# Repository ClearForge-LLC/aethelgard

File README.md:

# Aethelgard

Generates a circuit board and the firmware that drives it from one specification, and refuses to call either finished until the pair has survived simulated electrical and software faults together, before any board is manufactured.

**Status:** phases P0 to P2 are complete. P3's work has merged, and its exit gate waits on the bench rows that need the sensors (first silicon ran on 2026-11-16). P4's flight-controller work is under way. P5, a second chip family and firmware ecosystem judged as one combination (`docs/northstar.md` §3.1), waits on its trigger. **Use the engine image by its digest, as the Quickstart below does: it is the supported interface.** The crates.io release is 0.3.0 (2026-11-28), all eleven crates: `cargo install aethelgard-cli --version 0.3.0 --locked` installs `aethelgard`, which reads specification 31. Like every release it is a pinned snapshot with no update promise (`RUL-21`), and `main` moves past it. From one specification, `aethelgard` does five things:

- solves the pin assignment;
- emits a schematic and a placed, routed board that pass KiCad's ERC and DRC;
- generates a typestate board crate whose register effects Kani proves (`aethelgard generate` writes it; `aethelgard verify` proves the generated harness);
- boots generated firmware in Renode;
- serves all of this over MCP.

P2 added analog co-simulation, fault campaigns, an archive that replays, and `attribute`, which names the electrical or software half a failure belongs to. **Its rise times are computed by ngspice from the specification's declared pull-up and capacitance bound, not measured on the routed board** (`docs/architecture.md` `RUL-19`); P3 added `extract`, an upper bound on each I2C line's capacitance read from the routed board and judged against that declared bound, as a gate of `aethelgard verify`; `verify --fab-out` writes the reference probe's fabrication package only when every gate passes, and its verdict names every file's hash. No board has been made from it; the bench comparison waits for the development board. The code is licensed `MIT OR Apache-2.0` (see `LICENSE-MIT` and `LICENSE-APACHE`). KiCad's vendored symbols and footprints, in `crates/aethelgard-kicad-lib`, stay `CC-BY-SA-4.0`. Boards emitted from them carry no obligation.

## Where to go

| I want to know | Read |
|---|---|
| Why this exists and what must stay true | [`docs/northstar.md`](docs/northstar.md) |
| What it is and how it is shaped | [`docs/architecture.md`](docs/architecture.md) |
| What order it gets built in, and what "done" means | [`docs/roadmap.md`](docs/roadmap.md) |
| The planning conversation these were synthesized from | [`docs/inputs/argon-session/`](docs/inputs/argon-session/) |

## Quickstart

With only Docker, `bash`, `curl` and `sha256sum`: this block fetches the pinned reference specification, pulls the engine image by digest, and shows the reference board pass ERC and DRC and a doubly-assigned pin refused by name. CI runs exactly this block (`.github/workflows/quickstart.yml`), so it cannot drift. The block is one subshell with `set -euo pipefail`, so pasted into a terminal it stops at the first failed check and never closes your shell.

<!-- quickstart:begin -->
```bash
(
set -euo pipefail
IMAGE=ghcr.io/clearforge-llc/aethelgard@sha256:59e9f0aa2e1ee6ab48aa12855b659fae7ca9a5e9a43046f9d1c1cede9ffdce62
SPEC=https://raw.githubusercontent.com/ClearForge-LLC/aethelgard/10806528ce75ab9b17fdf09f5eda360ae78c7cf8/examples/sentinel-01-minimal.json

# The reference specification, checked against its hash.
curl -fsSL -o spec.json "$SPEC"
echo "03a82a043d459930e254adf5ef24bc5899efe2f5507d29e1c717f315c7bfe7ea  spec.json" | sha256sum -c -

docker pull -q "$IMAGE"
# HOME is the run directory, so the CLI's scratch is private to you (AET-WO-1601).
ae() { docker run --rm --user "$(id -u):$(id -g)" -e HOME=/work -v "$PWD:/work" -w /work "$IMAGE" aethelgard "$@"; }

# Emit the schematic, bill of materials and routed board (exit 0).
emit=$(ae emit --file spec.json --out out); echo "$emit"
grep -q '"ok":true' <<< "$emit"

# ERC on the schematic: exit 0 and a pass verdict.
erc=$(ae check erc --schematic out/sentinel-01.kicad_sch); echo "$erc"
grep -q '"verdict":"pass"' <<< "$erc"

# DRC on the board, judged by the rules the specification declares (board.rules), with schematic parity.
drc=$(ae check drc --board out/sentinel-01.kicad_pcb --spec spec.json --schematic out/sentinel-01.kicad_sch); echo "$drc"
grep -q '"verdict":"pass"' <<< "$drc"
grep -q '"findings":\[\]' <<< "$drc"

# Claim one pin twice (the I2C data line and the flash chip select, both on PB9). solve refuses: exit 2.
docker run --rm --user "$(id -u):$(id -g)" -v "$PWD:/work" -w /work "$IMAGE" python3 -I -c '
import json
s = json.load(open("spec.json"))
s["i2c_buses"][0]["sda"]["pin"] = "PB9"
s["spi_devices"][0]["cs"]["pin"] = "PB9"
json.dump(s, open("double.json", "w"))'
rc=0; refused=$(ae solve --file double.json) || rc=$?; echo "$refused"
[ "$rc" -eq 2 ]
grep -q '"kind":"PinClaimedTwice"' <<< "$refused"
grep -q '"claimants":\["i2c_buses\[0\].sda","spi_devices\[0\].cs"\]' <<< "$refused"
echo "quickstart ok"
)
```
<!-- quickstart:end -->

## Running it

**From crates.io, with no image:** `cargo install aethelgard-cli --version 0.3.0 --locked`. `validate` and `solve` are pure Rust and need no external tool; the release reads specification 31:

```bash
aethelgard validate < examples/sentinel-01-minimal.json   # {"ok":true,...}, exit 0
```

Everything that runs KiCad, Renode, ngspice or Kani (`check erc`, `check drc`, the twin, `prove`, `verify`) needs those tools, which the image above carries, and runs them only inside the CLI's own sandbox; without them the CLI refuses with a named kind and a nonzero exit (the codes are in [`crates/aethelgard-cli/README.md`](crates/aethelgard-cli/README.md)). For a checked board, use the image.

From a clone:

Check a specification. It prints one line of JSON and exits 0 when the specification is valid, nonzero otherwise; the codes are in [`crates/aethelgard-cli/README.md`](crates/aethelgard-cli/README.md).

```bash
cargo run -q -p aethelgard-cli -- validate < examples/sentinel-01-minimal.json
```

---

This README points; it does not define. The invariants, the rulings, and the phases each have exactly one home above, and a copy here would be a fourth place for the same fact to drift.

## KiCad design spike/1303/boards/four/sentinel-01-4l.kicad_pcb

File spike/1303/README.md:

# AET-WO-1303 spike probes (deleted at the build)

Python 3 with numpy, scipy (any recent); no network. Run from each directory.

- `boards/`: `aethelgard emit` of `examples/sentinel-01-minimal.json` (`ref/`) and
  `crates/aethelgard-cli/tests/fixtures/four-layer.json` (`four/`) at `121344d`, with `extract` output.
- `s3/`: the certified odd-mode C bracket (`bracket.py`).
  - `run_exact.py` → `exact.out`: against Cohn's exact coupled stripline.
  - `run_usb.py` → `usb.out`: IPC-2141 against the bracket; Z intervals over the 4-layer stackup; 1305's shell trial.
  - `run_sens.py` → `sens.out`: what widens the interval.
  - `run_nested.py` → `nested.out`: `microstrip_odd`'s bounds under nested refinement.
- `s4/`: the Thomson resistance bound (`rbound.py` pieces, `rbound2.py` graph and per-path recomputation, `pcb.py`).
  - `run_paths2.py conditions.json` → `paths.out`: the reported bounds, hole anywhere within ±0.075 mm.
  - `run_paths2.py conditions-concentric.json` → `paths-concentric.out`: the same, hole concentric (a condition).
  - `run_paths.py` → `paths-v1-inadmissible.out`: the first version, kept as the record of FEEDBACK F7; not a bound.
  - `check_exact.py` → `check_exact.out`: bar, annulus, barrel, 90° bend bracket, transfer resistance.
  - `check_barrel.py` → `check_barrel.out`: the spread barrel against a certified lower bound on the unrolled sheet.
  - `check_offset.py` → `check_offset.out`: hole-offset sensitivity of the via entry.
  - `check_fan_plane.py` → `check_fan_plane.out`: the bowtie against the exact two-hole sheet; the general fan and the pad pass against certified lower bounds; via-entry admissibility by brute force.
- `img.sh`: the capped container runner, by the architect's replaced rule 3 (a capped systemd user scope plus `podman --cgroups=disabled`). `caps.log` is its read-back; its first line is the earlier flag-based runner's stop (FEEDBACK D9).
- `p47/`: P4.7. `prep/` is a standalone probe that prepares a board as the DRC gate does. `prepared/` holds the 4-layer board so prepared, and `prepared/out/` its refilled `In1`/`In2` Gerbers. `out/` holds the unprepared board's (`boards/four/`, copied in for the run). `analyse.py` → `analyse.out`.
- `research-sources.md`: the research pass's record, labelled.

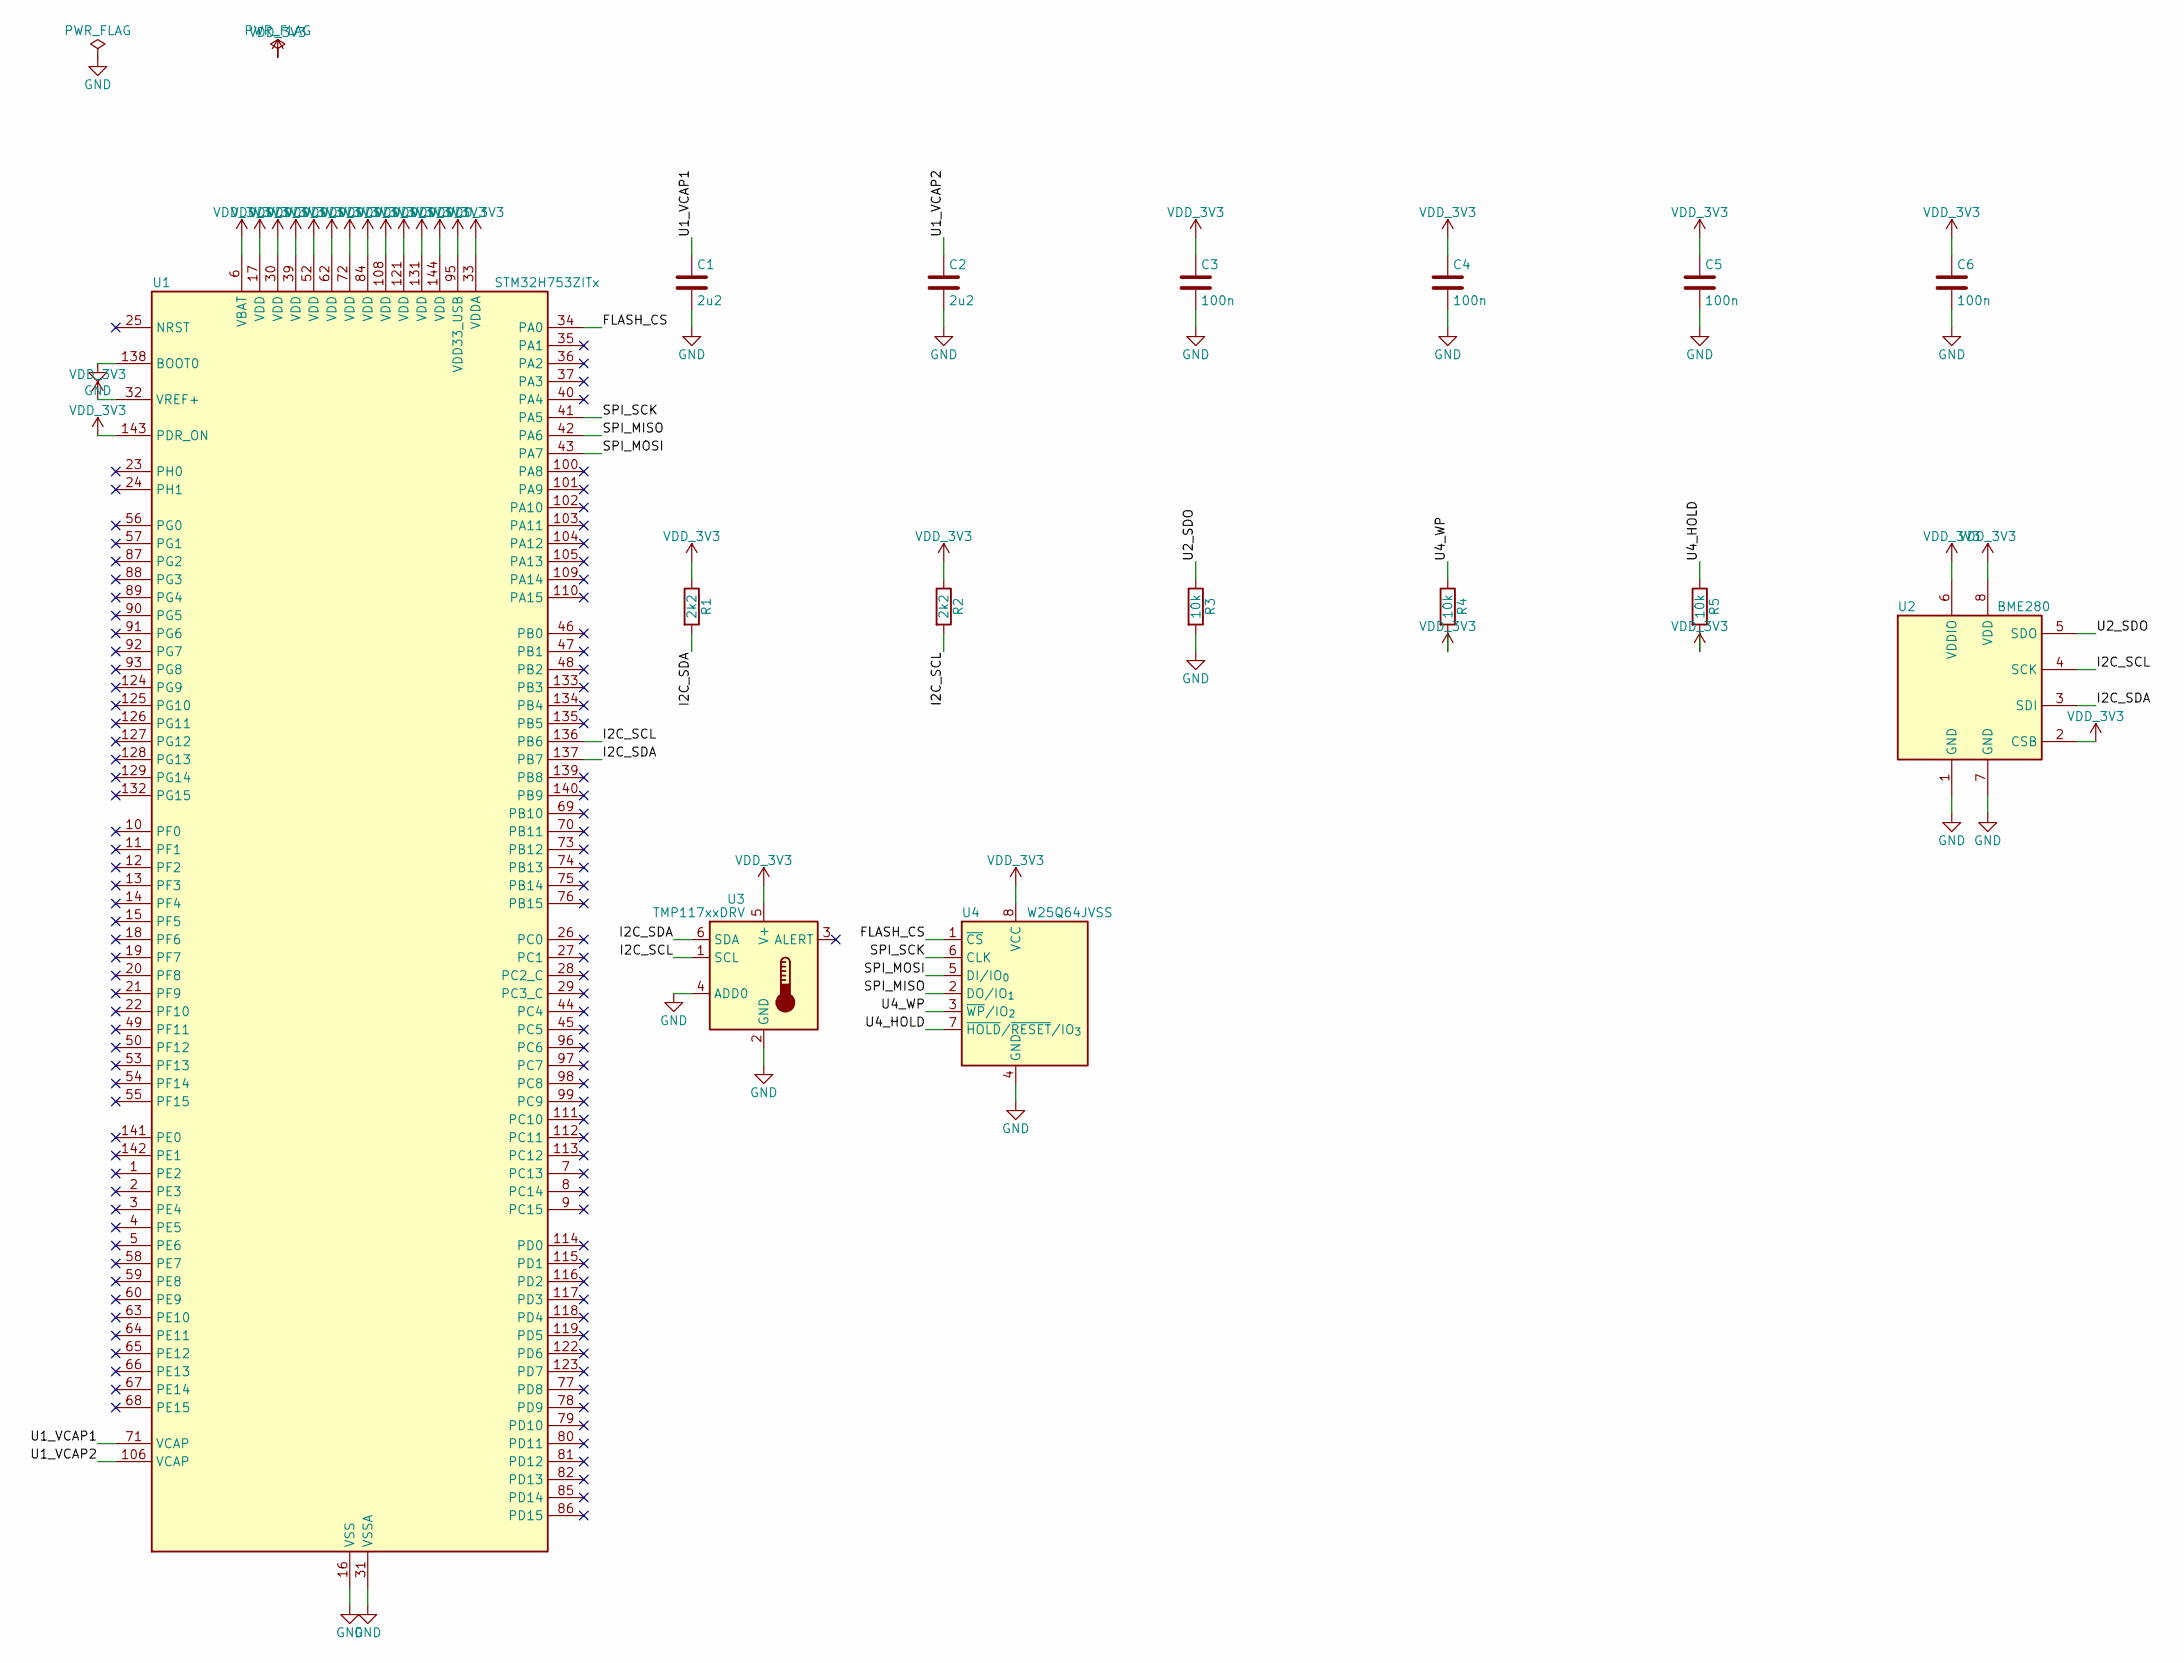
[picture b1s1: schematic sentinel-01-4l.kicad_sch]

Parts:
C1, C2: 2u2; C_0402_1005Metric
C3, C4, C5, C6: 100n; C_0402_1005Metric
R1, R2: 2k2; R_0402_1005Metric
R3, R4, R5: 10k; R_0402_1005Metric
U1: STM32H753ZITx; LQFP-144_20x20mm_P0.5mm
U2: BME280; Bosch_LGA-8_2.5x2.5mm_P0.65mm_ClockwisePinNumbering
U3: TMP117xxDRV; WSON-6-1EP_2x2mm_P0.65mm_EP1x1.6mm
U4: W25Q64JVSS; SOIC-8_5.3x5.3mm_P1.27mm

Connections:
/FLASH_CS: U1.34 (PA0), U4.1 (~CS)
/I2C_SCL: R2.2, U1.136 (PB6), U2.4 (SCK), U3.1 (SCL)
/I2C_SDA: R1.2, U1.137 (PB7), U2.3 (SDI), U3.6 (SDA)
/SPI_MISO: U1.42 (PA6), U4.2 (DO/IO_{1})
/SPI_MOSI: U1.43 (PA7), U4.5 (DI/IO_{0})
/SPI_SCK: U1.41 (PA5), U4.6 (CLK)
/U1_VCAP1: C1.1, U1.71 (VCAP)
/U1_VCAP2: C2.1, U1.106 (VCAP)
/U2_SDO: R3.1, U2.5 (SDO)
/U4_HOLD: R5.1, U4.7 (~HOLD/~RESET/IO_{3})
/U4_WP: R4.1, U4.3 (~WP/IO_{2})
GND: C1.2, C2.2, C3.2, C4.2, C5.2, C6.2, R3.2, U1.16 (VSS), U1.31 (VSSA), U1.38 (VSS), U1.51 (VSS), U1.61 (VSS), U1.83 (VSS), U1.94 (VSS), U1.107 (VSS), U1.120 (VSS), U1.130 (VSS), U1.138 (BOOT0), U2.1 (GND), U2.7 (GND), U3.2 (GND), U3.4 (ADD0), U4.4 (GND)
VDD_3V3: C3.1, C4.1, C5.1, C6.1, R1.1, R2.1, R4.2, R5.2, U1.6 (VBAT), U1.17 (VDD), U1.30 (VDD), U1.32 (VREF+), U1.33 (VDDA), U1.39 (VDD), U1.52 (VDD), U1.62 (VDD), U1.72 (VDD), U1.84 (VDD), U1.95 (VDD33_USB), U1.108 (VDD), U1.121 (VDD), U1.131 (VDD), U1.143 (PDR_ON), U1.144 (VDD), U2.2 (CSB), U2.6 (VDDIO), U2.8 (VDD), U3.5 (V+), U4.8 (VCC)

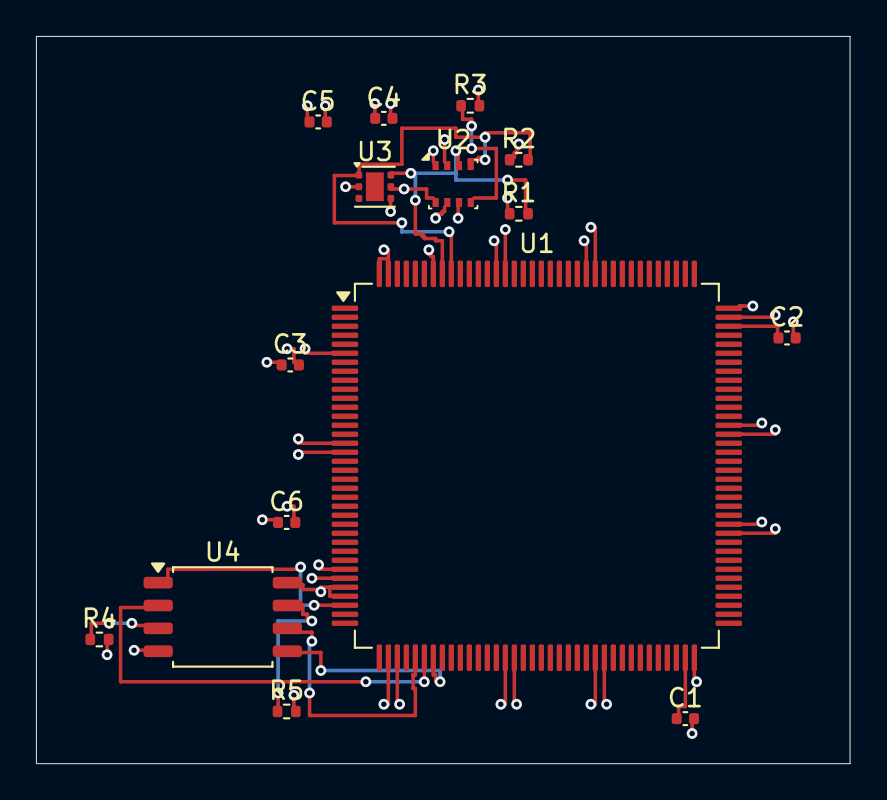
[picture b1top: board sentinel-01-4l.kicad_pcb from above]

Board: 4 copper layers, 45.2 x 40.4 mm, 15 parts (0 on the bottom side), 13 nets.

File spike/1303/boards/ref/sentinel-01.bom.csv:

Reference,Value,Footprint,Symbol,Note
C1,2u2,Capacitor_SMD:C_0402_1005Metric,Device:C,
C2,2u2,Capacitor_SMD:C_0402_1005Metric,Device:C,
C3,100n,Capacitor_SMD:C_0402_1005Metric,Device:C,
C4,100n,Capacitor_SMD:C_0402_1005Metric,Device:C,
C5,100n,Capacitor_SMD:C_0402_1005Metric,Device:C,
C6,100n,Capacitor_SMD:C_0402_1005Metric,Device:C,
R1,2k2,Resistor_SMD:R_0402_1005Metric,Device:R,
R2,2k2,Resistor_SMD:R_0402_1005Metric,Device:R,
R3,10k,Resistor_SMD:R_0402_1005Metric,Device:R,
R4,10k,Resistor_SMD:R_0402_1005Metric,Device:R,
R5,10k,Resistor_SMD:R_0402_1005Metric,Device:R,
U1,STM32H753ZITx,Package_QFP:LQFP-144_20x20mm_P0.5mm,MCU_ST_STM32H7:STM32H753ZITx,
U2,BME280,Package_LGA:Bosch_LGA-8_2.5x2.5mm_P0.65mm_ClockwisePinNumbering,Sensor:BME280,
U3,TMP117xxDRV,Package_SON:WSON-6-1EP_2x2mm_P0.65mm_EP1x1.6mm,Sensor_Temperature:TMP117xxDRV,
U4,W25Q64JVSS,Package_SO:SOIC-8_5.3x5.3mm_P1.27mm,Memory_Flash:W25Q32JVSS,"symbol Memory_Flash:W25Q32JVSS stands in for W25Q64JV: same family, same SOIC-8 208-mil pinout (AET-WO-1300 D2)"

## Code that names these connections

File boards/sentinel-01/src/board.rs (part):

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    false
}

/// `PA0`, net `FLASH_CS`: a GPIO output.
pub struct PA0<M> {
    _mode: PhantomData<M>,
}

impl PA0<Unconfigured> {
    pub fn into_output<R: Registers>(self, r: &mut R) -> PA0<Output> {
        r.modify(TOKEN, Block::GpioA, 0x08, |v| v & !0x00000003);
        r.write(TOKEN, Block::GpioA, 0x18, 0x00000001);
        r.modify(TOKEN, Block::GpioA, 0x00, |v| (v & !0x00000003) | 0x00000001);
        PA0 { _mode: PhantomData }
    }
}

impl PA0<Output> {
    pub fn set_high<R: Registers>(&mut self, r: &mut R) {
        r.write(TOKEN, Block::GpioA, 0x18, 0x00000001);
    }
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    }
}

/// `PA5`, net `SPI_SCK`: `SPI1_SCK` on AF5.
pub struct PA5<M> {
    _mode: PhantomData<M>,
}

impl PA5<Unconfigured> {
    pub fn into_spi1_sck<R: Registers>(self, r: &mut R) -> PA5<AlternateFunction<5>> {
        r.modify(TOKEN, Block::GpioA, 0x08, |v| (v & !0x00000c00) | 0x00000400);
        r.modify(TOKEN, Block::GpioA, 0x20, |v| (v & !0x00f00000) | 0x00500000);
        r.modify(TOKEN, Block::GpioA, 0x00, |v| (v & !0x00000c00) | 0x00000800);
        PA5 { _mode: PhantomData }
    }
}

/// `PA6`, net `SPI_MISO`: `SPI1_MISO` on AF5.
pub struct PA6<M> {
    _mode: PhantomData<M>,
}

impl PA6<Unconfigured> {
    pub fn into_spi1_miso<R: Registers>(self, r: &mut R) -> PA6<AlternateFunction<5>> {
        r.modify(TOKEN, Block::GpioA, 0x08, |v| v & !0x00003000);
        r.modify(TOKEN, Block::GpioA, 0x20, |v| (v & !0x0f000000) | 0x05000000);
        r.modify(TOKEN, Block::GpioA, 0x00, |v| (v & !0x00003000) | 0x00002000);
        PA6 { _mode: PhantomData }
    }
}

/// `PA7`, net `SPI_MOSI`: `SPI1_MOSI` on AF5.
pub struct PA7<M> {
    _mode: PhantomData<M>,
}

impl PA7<Unconfigured> {
    pub fn into_spi1_mosi<R: Registers>(self, r: &mut R) -> PA7<AlternateFunction<5>> {
        r.modify(TOKEN, Block::GpioA, 0x08, |v| (v & !0x0000c000) | 0x00004000);
        r.modify(TOKEN, Block::GpioA, 0x20, |v| (v & !0xf0000000) | 0x50000000);
        r.modify(TOKEN, Block::GpioA, 0x00, |v| (v & !0x0000c000) | 0x00008000);
        PA7 { _mode: PhantomData }
    }
}

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    }
}

/// `PB6`, net `I2C_SCL`: `I2C1_SCL` on AF4.
pub struct PB6<M> {
    _mode: PhantomData<M>,
}

impl PB6<Unconfigured> {
    pub fn into_i2c1_scl<R: Registers>(self, r: &mut R) -> PB6<AlternateFunction<4>> {
        r.modify(TOKEN, Block::GpioB, 0x08, |v| v & !0x00003000);
        r.modify(TOKEN, Block::GpioB, 0x20, |v| (v & !0x0f000000) | 0x04000000);
        r.modify(TOKEN, Block::GpioB, 0x00, |v| (v & !0x00003000) | 0x00002000);
        PB6 { _mode: PhantomData }
    }
}

/// `PB7`, net `I2C_SDA`: `I2C1_SDA` on AF4.
pub struct PB7<M> {
    _mode: PhantomData<M>,
}

impl PB7<Unconfigured> {
    pub fn into_i2c1_sda<R: Registers>(self, r: &mut R) -> PB7<AlternateFunction<4>> {
        r.modify(TOKEN, Block::GpioB, 0x08, |v| v & !0x0000c000);
        r.modify(TOKEN, Block::GpioB, 0x20, |v| (v & !0xf0000000) | 0x40000000);
        r.modify(TOKEN, Block::GpioB, 0x00, |v| (v & !0x0000c000) | 0x00008000);
        PB7 { _mode: PhantomData }
    }
}

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
/// The solved pins of port A.
pub struct GpioAPins {
    pub pa0: PA0<Unconfigured>,
    pub pa10: PA10<Unconfigured>,
    pub pa5: PA5<Unconfigured>,
    pub pa6: PA6<Unconfigured>,
    pub pa7: PA7<Unconfigured>,
    pub pa9: PA9<Unconfigured>,
}

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        r.write(TOKEN, Block::GpioA, 0x04, 0x00000000);
        r.write(TOKEN, Block::GpioA, 0x0c, 0x64000000);
        GpioAPins {
            pa0: PA0 { _mode: PhantomData },
            pa10: PA10 { _mode: PhantomData },
            pa5: PA5 { _mode: PhantomData },
            pa6: PA6 { _mode: PhantomData },
            pa7: PA7 { _mode: PhantomData },
            pa9: PA9 { _mode: PhantomData },
        }
    }
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
/// The solved pins of port B.
pub struct GpioBPins {
    pub pb6: PB6<Unconfigured>,
    pub pb7: PB7<Unconfigured>,
}

impl GpioB<Clocked> {
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        r.write(TOKEN, Block::GpioB, 0x04, 0x000000c0);
        r.write(TOKEN, Block::GpioB, 0x0c, 0x00000100);
        GpioBPins {
            pb6: PB6 { _mode: PhantomData },
            pb7: PB7 { _mode: PhantomData },
        }
    }
}
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        self,
        r: &mut R,
        _clock: &ResetClock,
        _scl: PB6<AlternateFunction<4>>,
        _sda: PB7<AlternateFunction<4>>,
    ) -> I2c1<Enabled<S>> {
        r.write(TOKEN, Block::I2c1, 0x00, 0x00000000);
        r.write(TOKEN, Block::I2c1, 0x10, S::TIMINGR);
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/// F3).
pub struct Spi1Selects {
    /// `U4`'s, net `FLASH_CS`.
    pub pa0: PA0<Output>,
}

/// The devices on `SPI1`, in the specification's order: each reference,
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#[allow(non_camel_case_types)]
#[derive(Clone, Copy, PartialEq, Eq, Debug)]
pub enum Spi1Device {
    /// `U4`, a `W25Q64JVxIQ`, chip select `PA0`.
    U4,
}

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        self,
        r: &mut R,
        _clock: &ResetClock,
        _sck: PA5<AlternateFunction<5>>,
        _mosi: PA7<AlternateFunction<5>>,
        _miso: PA6<AlternateFunction<5>>,
        _selects: Spi1Selects,
    ) -> Spi1<Enabled<()>> {
        r.write(TOKEN, Block::GpioA, 0x18, 0x00000001);
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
